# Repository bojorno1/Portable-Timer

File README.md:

<h1>Portable Timer!</h1>
<br><h2><em>A timer that you can take with you!</em></h2>

<br>This is Portable Timer! It's a small timer that you can take with you <em>anywhere!</em> Take it with you to the beach, the car, or even to outer space! The possibilities are limitless! Now, you may be wondering, <em>Why don't you just use a timer on your phone?</em> My answer to that is <em><strong>Where's the fun in that???</strong></em>

<br><br>This project is made up of 4 boards:
The Main Board, found <a href="https://github.com/bojorno1/Portable-Timer/tree/main/boards/Main_Board"> here... </a>

<br>The Button Board, found <a href="https://github.com/bojorno1/Portable-Timer/tree/main/boards/Button_board">here...</a>

<br>The I2C Backpack (thanks to <a href="http://electronicsgate.com/Images/lcd_backpack/schematic.png">electronics gate</a> for making a great base on how to make one of these!) found <a href="https://github.com/bojorno1/Portable-Timer/tree/main/boards/I2CBackpack">here...</a>

<br>and finally...

<br>The Battery Board, found <a href="https://github.com/bojorno1/Portable-Timer/tree/main/boards/Battery_Board">here...</a>

<br>These 4 boards all connect together with jumper wires, as shown in the PCB Schematic, found <a href="https://github.com/bojorno1/Portable-Timer/blob/main/boards/schematic.pdf">here...</a>

The firmware files are found <a href="https://github.com/bojorno1/Portable-Timer/tree/main/firmware">here...</a>

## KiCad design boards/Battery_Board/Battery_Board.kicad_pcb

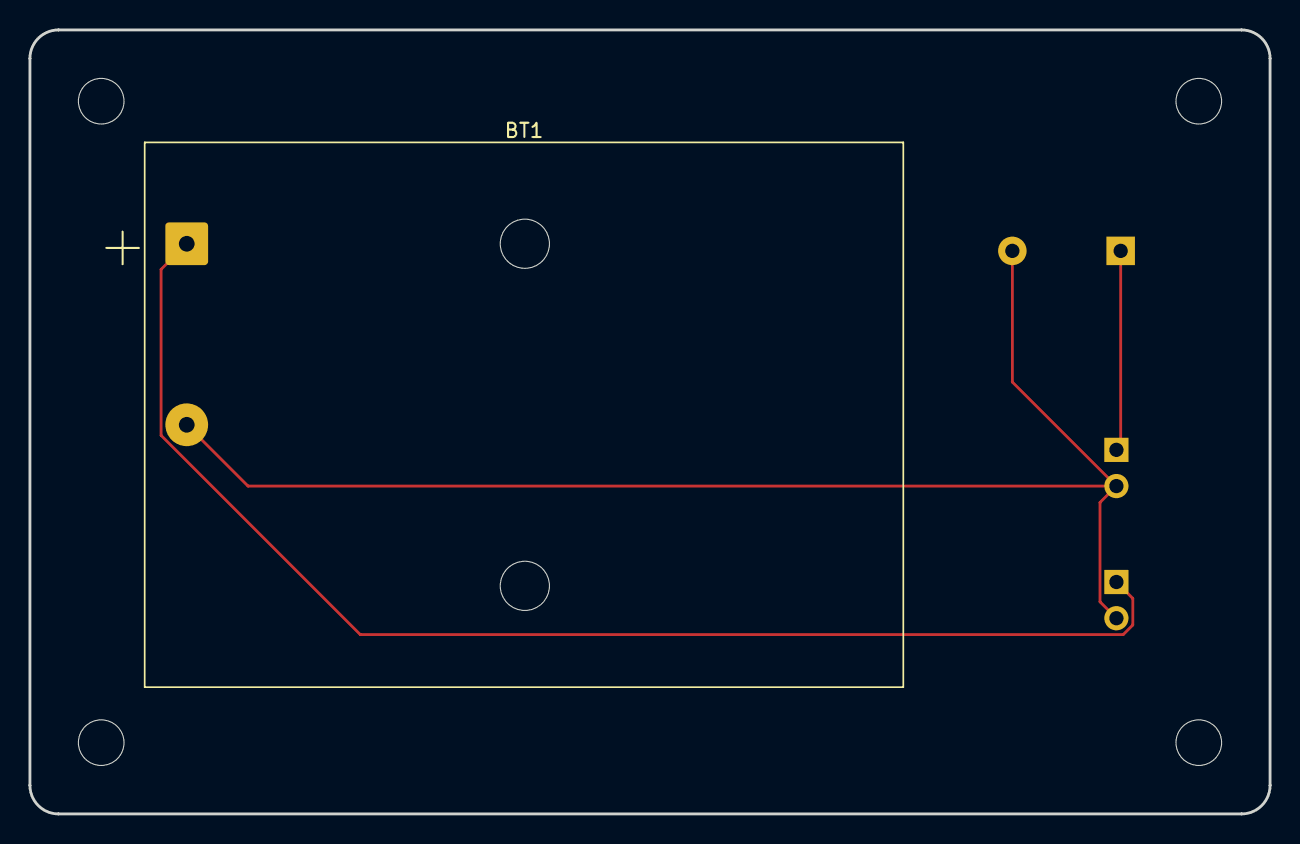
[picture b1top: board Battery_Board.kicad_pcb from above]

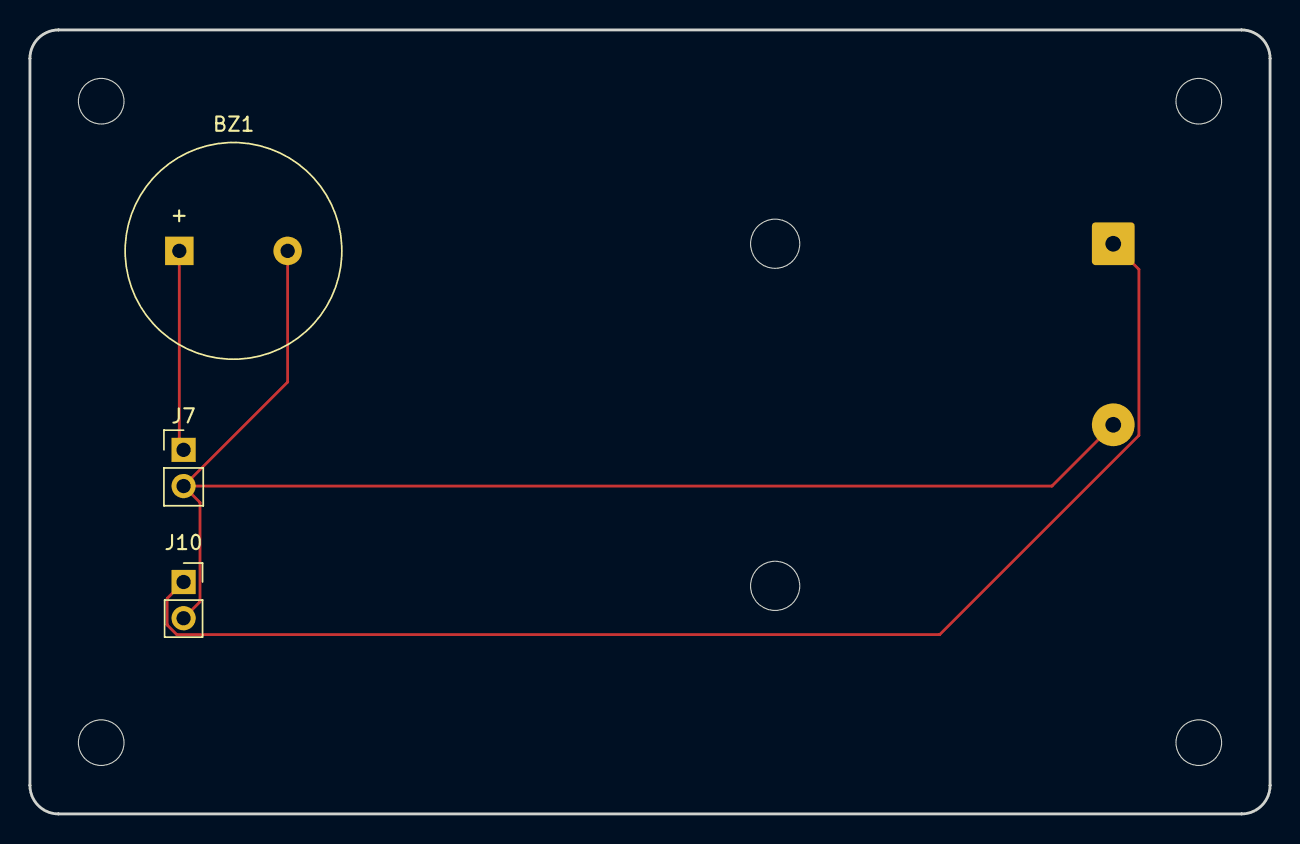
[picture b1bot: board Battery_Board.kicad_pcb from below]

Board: 64 copper layers, 87.0 x 55.0 mm, 4 parts (3 on the bottom side), 3 nets.

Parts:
BT1: Battery; BatteryHolder_Keystone_2479_3xAAA
BZ1: Buzzer; Buzzer_15x7.5RM7.6
J7: BuzzerPin; PinHeader_1x02_P2.54mm_Vertical
J10: BatteryConnector; PinSocket_1x02_P2.54mm_Vertical

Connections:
/BatteryPlus: BT1.1 (+), J10.1
/Buzzer: BZ1.1 (+), J7.1
GND: BT1.2 (-), BZ1.2 (-), J7.2, J10.2

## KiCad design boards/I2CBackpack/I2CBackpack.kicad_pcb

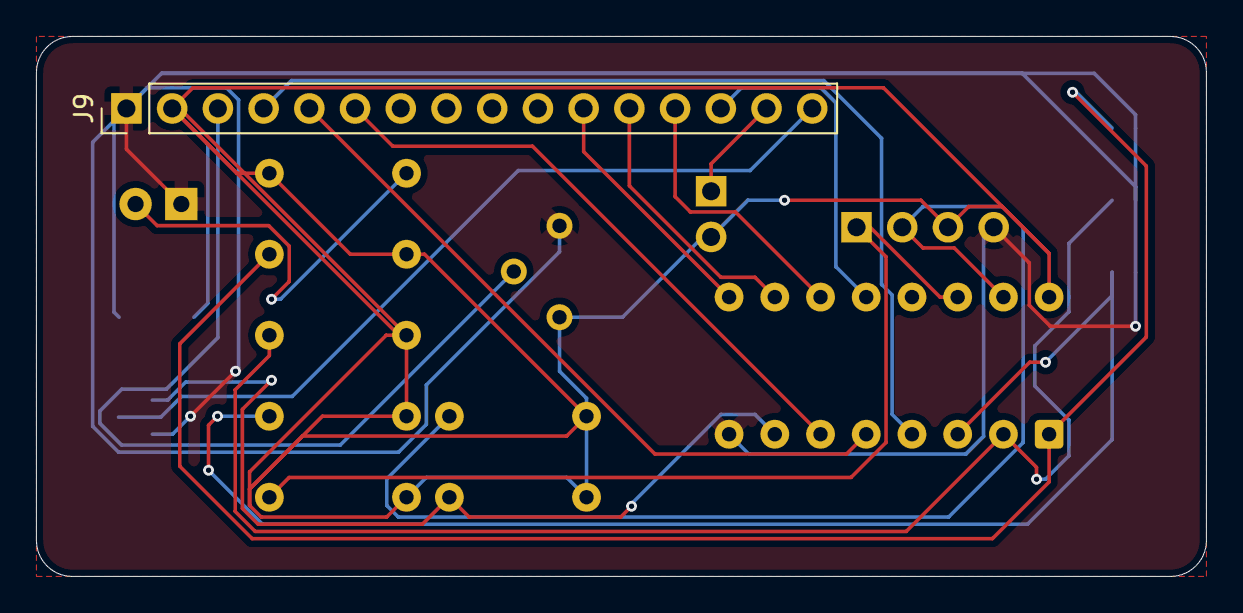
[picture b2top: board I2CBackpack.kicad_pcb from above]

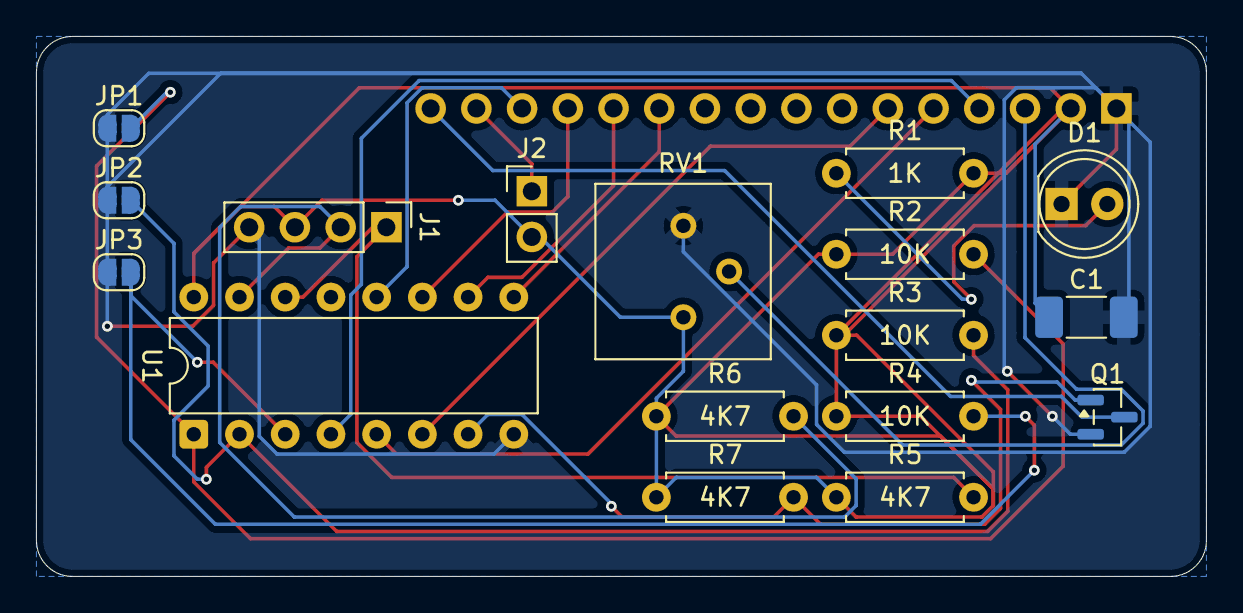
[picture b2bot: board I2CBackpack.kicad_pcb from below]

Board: 64 copper layers, 65.0 x 30.0 mm, 18 parts (17 on the bottom side), 19 nets.

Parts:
C1: 100nF; C_1808_4520Metric
D1: LED; LED_D5.0mm
J1: DisplayPin; PinHeader_1x04_P2.54mm_Vertical
J2: Jumper; PinHeader_1x02_P2.54mm_Vertical
J9: DisplayModulePin; PinHeader_1x16_P2.54mm_Vertical
JP1, JP2, JP3: SolderJumper_2_Open; SolderJumper-2_P1.3mm_Open_RoundedPad1.0x1.5mm
Q1: BC850; SOT-23
R1: 1K; R_Axial_DIN0207_L6.3mm_D2.5mm_P7.62mm_Horizontal
R2, R3, R4: 10K; R_Axial_DIN0207_L6.3mm_D2.5mm_P7.62mm_Horizontal
R5, R6, R7: 4K7; R_Axial_DIN0207_L6.3mm_D2.5mm_P7.62mm_Horizontal
RV1: R_Potentiometer_Trim; Potentiometer_Bourns_3386P_Vertical
U1: PCF8574AP; DIP-16_W7.62mm

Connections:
+3V3: C1.1, J1.3, J2.2, J9.2, R1.2, R2.1, R3.1, R4.1, R5.1, R6.1, R7.1, RV1.1, U1.16 (VDD)
/A/VEE: J2.1, J9.15
/DB4: J9.11, U1.9 (P4)
/DB5: J9.12, U1.10 (P5)
/DB6: J9.13, U1.11 (P6)
/DB7: J9.14, U1.12 (P7)
/E: J9.6, U1.6 (P2)
/K: J9.16, Q1.3 (C)
/RS: J9.4, U1.4 (P0)
/R/W: J9.5, U1.5 (P1)
/SCL: J1.1, R5.2, U1.14 (SCL)
/SDA: J1.2, R6.2, U1.15 (SDA)
/V0: J9.3, RV1.2
GND: C1.2, D1.1 (K), J1.4, J9.1, JP1.1 (A), JP2.1 (A), JP3.1 (A), Q1.2 (E), RV1.3, U1.8 (GND)
unnamed: D1.2 (A), R1.1
unnamed: JP1.2 (B), R2.2, U1.1 (A0)
unnamed: JP2.2 (B), R3.2, U1.2 (A1)
unnamed: JP3.2 (B), R4.2, U1.3 (A2)
unnamed: Q1.1 (B), R7.2, U1.7 (P3)

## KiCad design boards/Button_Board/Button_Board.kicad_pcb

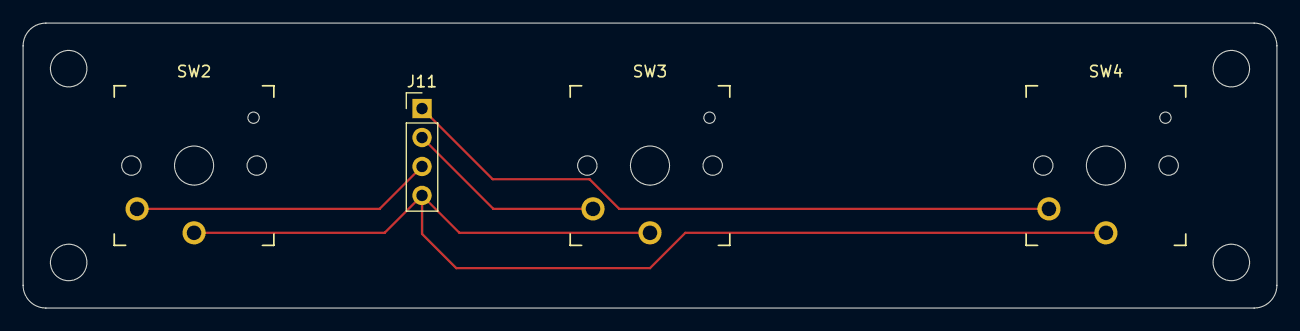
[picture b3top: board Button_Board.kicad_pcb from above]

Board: 64 copper layers, 110.0 x 25.0 mm, 4 parts (0 on the bottom side), 4 nets.

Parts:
J11: ButtonPin; PinHeader_1x04_P2.54mm_Vertical
SW2, SW3, SW4: SW_Push; Kailh Choc Low-Profile Switches

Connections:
/Center: J11.2, SW3.2
/Left: J11.3, SW2.2
/Right: J11.1, SW4.2
GND: J11.4, SW2.1, SW3.1, SW4.1

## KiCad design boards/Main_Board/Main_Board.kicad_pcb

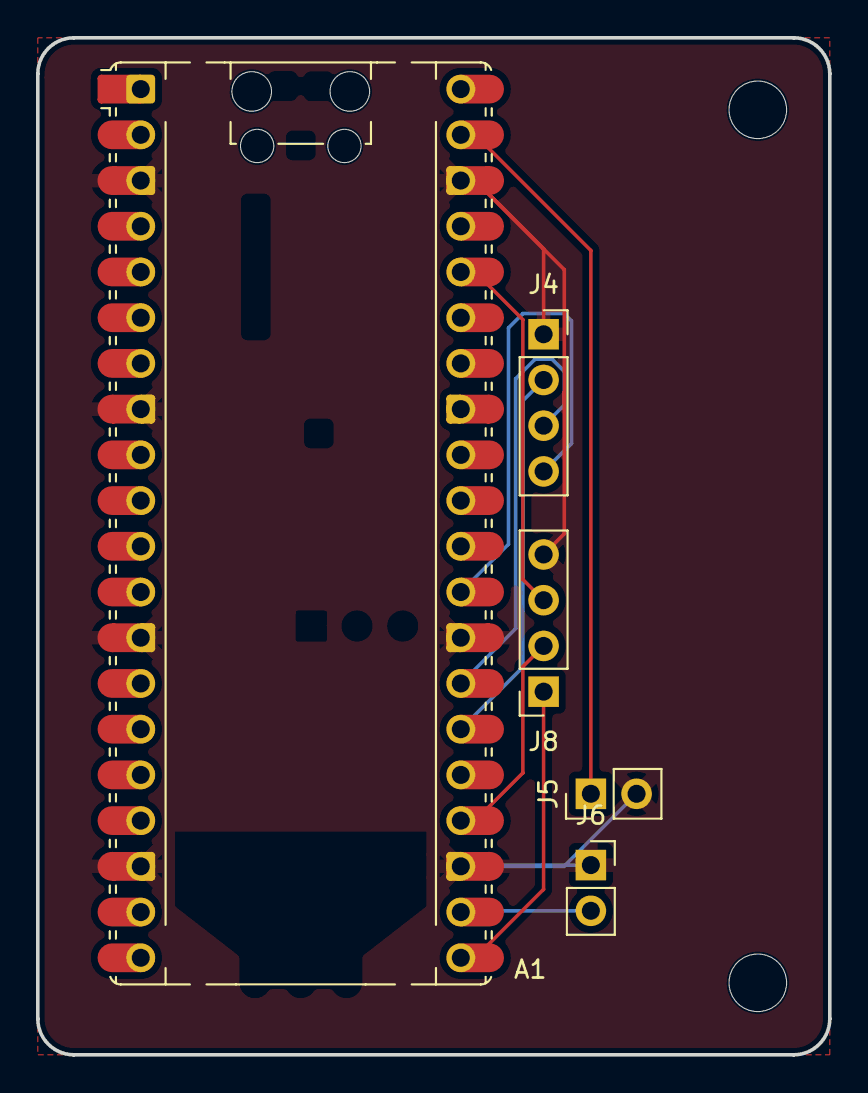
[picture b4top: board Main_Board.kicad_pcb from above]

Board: 64 copper layers, 44.0 x 56.5 mm, 6 parts (0 on the bottom side), 9 nets.

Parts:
A1: RaspberryPi_Pico; RaspberryPi_Pico_Common_Unspecified
Buzzer: MountingHole_3.2mm_M3
J4: ButtonConnector; PinSocket_1x04_P2.54mm_Vertical
J5: BatteryPin; PinHeader_1x02_P2.54mm_Vertical
J6: BuzzerConnector; PinSocket_1x02_P2.54mm_Vertical
J8: DisplayConnector; PinSocket_1x04_P2.54mm_Vertical

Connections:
+3V3: A1.36 (3V3), J8.3
/BatteryPlus: A1.39 (VSYS), J5.1
/Buzzer: A1.22 (GPIO17), J6.2
/Center: A1.27 (GPIO21), J4.3
/Left: A1.29 (GPIO22), J4.4
/Right: A1.26 (GPIO20), J4.2
/SCL: A1.21 (GPIO16), J8.1
/SDA: A1.24 (GPIO18), J8.2
GND: A1.3 (GND), A1.8 (GND), A1.13 (GND), A1.18 (GND), A1.23 (GND), A1.28 (GND), A1.38 (GND), J4.1, J5.2, J6.1, J8.4
